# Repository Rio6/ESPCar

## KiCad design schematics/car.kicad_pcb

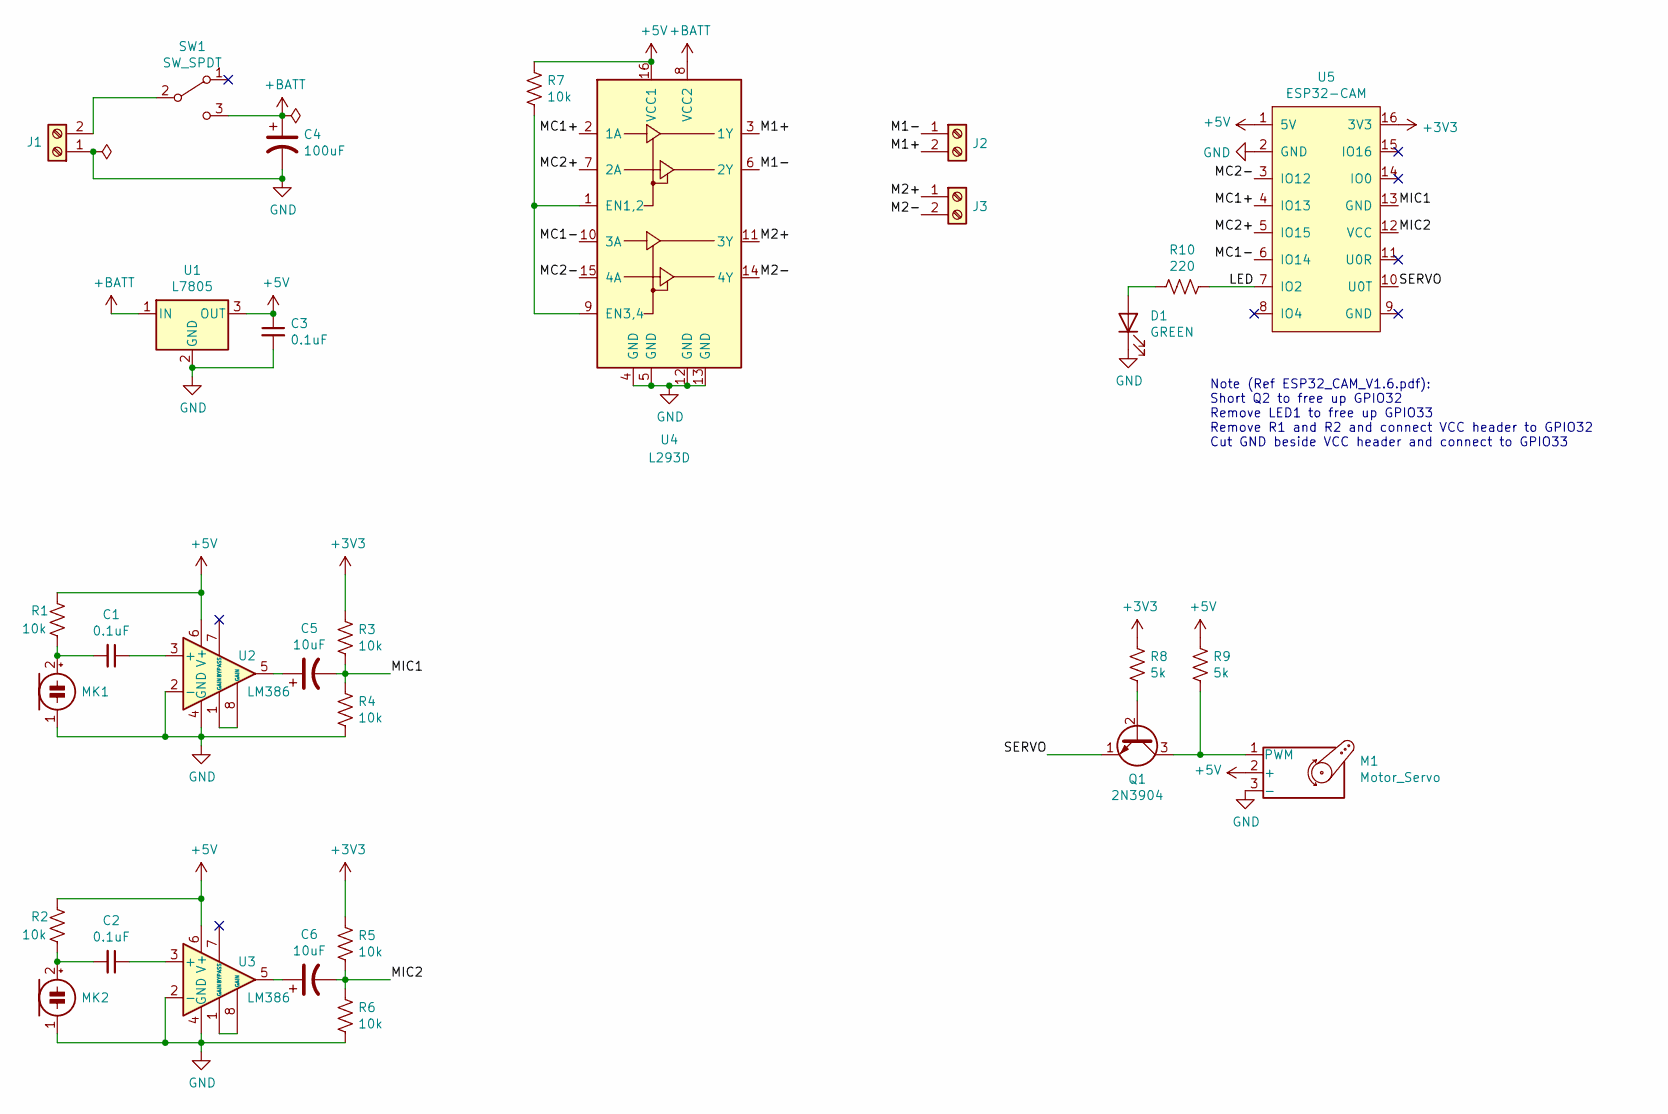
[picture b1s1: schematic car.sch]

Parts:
C1, C2, C3: 0.1uF; C_Disc_D3.0mm_W1.6mm_P2.50mm
C4: 100uF; CP_Radial_D6.3mm_P2.50mm
C5, C6: 10uF; CP_Radial_D6.3mm_P2.50mm
D1: GREEN; LED_D5.0mm
J1, J2, J3: Screw_Terminal_01x02; TerminalBlock_bornier-2_P5.08mm
M1: Motor_Servo; PinHeader_1x03_P2.54mm_Vertical
MK1, MK2: Microphone_Condenser; PinHeader_2x01_P2.54mm_Vertical
Q1: 2N3904; TO-92_Inline_Wide
R1, R2, R3, R4, R5, R6, R7: 10k; R_Axial_DIN0204_L3.6mm_D1.6mm_P7.62mm_Horizontal
R8, R9: 5k; R_Axial_DIN0204_L3.6mm_D1.6mm_P7.62mm_Horizontal
R10: 220; R_Axial_DIN0204_L3.6mm_D1.6mm_P7.62mm_Horizontal
SW1: SW_SPDT; SW_Slide_1P2T_CK_OS102011MS2Q
U1: L7805; TO-220-3_Vertical
U2, U3: LM386; DIP-8_W7.62mm
U4: L293D; DIP-16_W7.62mm_Socket
U5: ESP32-CAM

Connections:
+3V3: R3.1, R5.1, R8.1, U5.16 (3V3)
+5V: C3.1, M1.2 (+), R1.1, R2.1, R7.1, R9.1, U1.3 (OUT), U2.6 (V+), U3.6 (V+), U4.16 (VCC1), U5.1 (5V)
+BATT: C4.1, SW1.3 (C), U1.1 (IN), U4.8 (VCC2)
/LED: R10.1, U5.7 (IO2)
/M1+: J2.2, U4.3 (1Y)
/M1-: J2.1, U4.6 (2Y)
/M2+: J3.1, U4.11 (3Y)
/M2-: J3.2, U4.14 (4Y)
/MC1+: U4.2 (1A), U5.4 (IO13)
/MC1-: U4.10 (3A), U5.6 (IO14)
/MC2+: U4.7 (2A), U5.5 (IO15)
/MC2-: U4.15 (4A), U5.3 (IO12)
/MIC1: C5.2, R3.2, R4.1, U5.13 (GND)
/MIC2: C6.2, R5.2, R6.1, U5.12 (VCC)
/SERVO: Q1.1 (E), U5.10 (U0T)
GND: C3.2, C4.2, D1.1 (K), J1.1, M1.3 (-), MK1.1 (-), MK2.1 (-), R4.2, R6.2, U1.2 (GND), U2.2 (-), U2.4 (GND), U3.2 (-), U3.4 (GND), U4.4 (GND), U4.5 (GND), U4.12 (GND), U4.13 (GND), U5.2 (GND)
unnamed: C1.1, U2.3 (+)
unnamed: C1.2, MK1.2 (+), R1.2
unnamed: C2.1, U3.3 (+)
unnamed: C2.2, MK2.2 (+), R2.2
unnamed: C5.1, U2.5
unnamed: C6.1, U3.5
unnamed: D1.2 (A), R10.2
unnamed: J1.2, SW1.2 (B)
unnamed: M1.1 (PWM), Q1.3 (C), R9.2
unnamed: Q1.2 (B), R8.2
unnamed: R7.2, U4.1 (EN1,2), U4.9 (EN3,4)
unnamed: U2.1 (GAIN), U2.8 (GAIN)
unnamed: U3.1 (GAIN), U3.8 (GAIN)

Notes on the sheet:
Note (Ref ESP32_CAM_V1.6.pdf): Short Q2 to free up GPIO32 Remove LED1 to free up GPIO33 Remove R1 and R2 and connect VCC header to GPIO32 Cut GND beside VCC header and connect to GPIO33

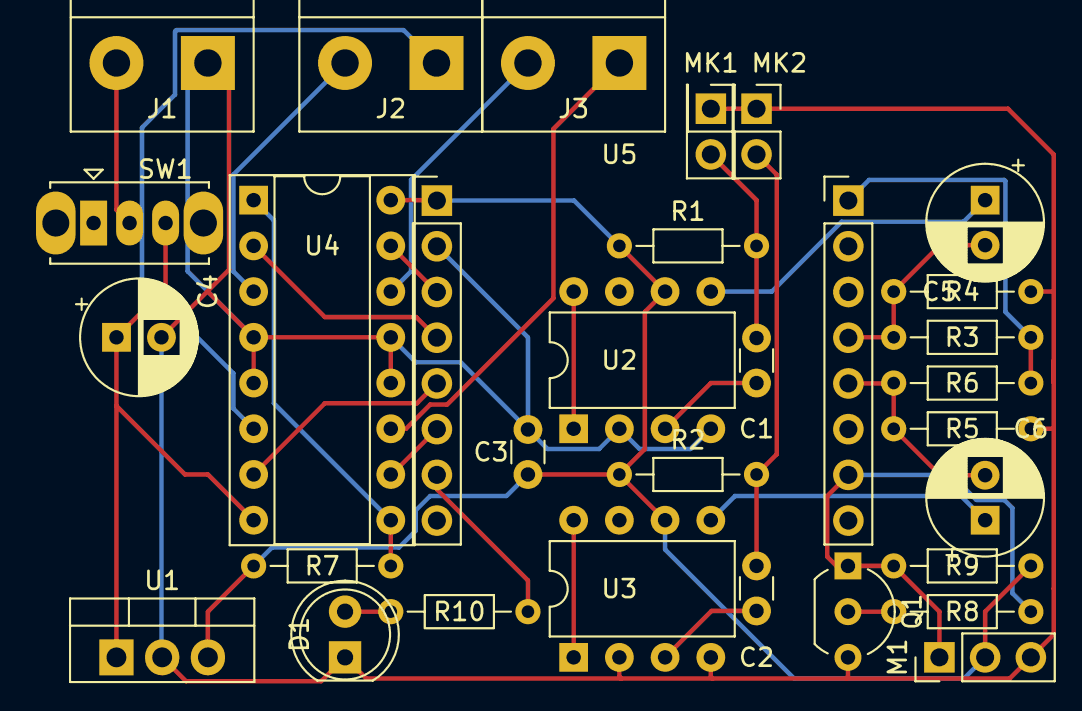
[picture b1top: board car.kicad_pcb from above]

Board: 2 copper layers, 30 parts (0 on the bottom side), 29 nets.

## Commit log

2021-12-30 schematics
2021-12-31 update layout
2021-12-31 simple test code
2022-01-01 add some cad models
2022-01-01 add more cad models
2022-01-01 add missing hex countersink
2022-01-03 add wifi and camera init code
2022-01-04 use blinking to indicate connection status
2022-01-05 split components into different files add add wip otp
2022-01-05 switch from pio to esp-idf
2022-01-05 fix some compilation and runtime errors
2022-01-06 fix CMake app name
2022-01-07 working ota
2022-01-08 stream camera through network wip
2022-01-09 working video receiving (disable ota for now)
2022-01-10 switch from socket api to to lwip api
2022-01-14 voice streaming test
2022-02-03 wip control via tcp
2022-02-04 switch to udp for controls
2022-02-05 send video only to connected clients
2022-02-05 add sdkconfig.default
2022-02-06 add status reporting
2022-02-06 reduce network overhead
2022-02-06 simple control program and make firmware working
2022-02-06 add mdns
2022-02-06 fix x y calculation range
